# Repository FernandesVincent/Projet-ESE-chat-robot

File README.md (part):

# Projet ESE – Chat Robot  

Le projet de Chat Robot développé dans le cadre de la spécialité ESE dirigée par M.Fiack et supervisée par lui et M. Papazogou s'est achevé le vendredi 16 Janvier 2026. 

Nous allons donc revenir ici sur les différents aspects notables du projet, notamment ceux où notre projet s'est détaché des consignes initiales.

Nous allons donc passer en revue les différentes parties du projet en commençant par une partie sur l'organisation du projet et des tâches attribuées aux différents membres de l'équipe puis nous aborderons la partie Hardware séparée en deux sous parties, l'une pour la modélisation 3D sous Onshape et l'autre pour la conception de PCB sous Kicad. Puis, nous aborderons la partie Software séparée en plusieurs parties, chachune abordant un composant important du projet. 

Par soucis de lisibilité de l'ensemble du document nous n'allons pas détaillé en profondeur toutes les parties et sous parties liées à la mise en place de chaque composant sur le PCB ou à leur programmation. À la place, nous expliquerons brièvement l'ensemble des logiques hardware et software pour ensuite analyser en profondeurs seulement certains aspects de ces parties.

## Organisation du Projet

Le projet a été porté par une équipe de quatres étudiants de 3ème année à l'ENSEA faisant partit de la spécialité ESE, cette équipe est composée de : 

- Vincent FERNANDES
- Paul CAILLAUD
- Kelly LUO
- Yimei Xia

Après diverses discussions au cours du semestre, voici comment ont été attribués les rôles concernant le projet : 

- Vincent : PCB, modélisation/impression 3D, Soudure CMS & THT, TOFs, Moteurs, LED, LiDAR, mise en commun du code sous FreeRTOS
- Paul : Modélisation 3D, cablâge, Soudure CMS & THT, Accéléromètre, Moteurs
- Kelly : Lidar
- Yimei : Accéléromètre

Par ailleurs un README relatant l'avancée à mi-parcours (13 Novembre) est disponible dans le dossier Gestion.

## Hardware

### Modélisation 3D

Pour notre projet, nous avons décidés d'utiliser un pack de batteries Li-ion 2S au lieu du pack de 5 batteries NIMH fournit à la base car cela nous apporte une stabilité de maintient de la tension aux bornes de la batterie ainsi qu'une simplicité de la recharge. En effet, pour recharger les batteries que nous utilisions il nous fallait simplement les connecter à n'importe quelle alimentation stabilisée à 8.4V et non pas un chargeur dédié comme pour les batteries NIMH.

Cela étant, dû au fait d'avoir modifier les batteries nous avons dû adapter notre modélisation 3D. Nous avons donc décider d'inclure la pack de batteries directement dans la base du robot comme présenté ci-dessous afin d'augmenter la stabilité de l'ensemble. Cependant, cela a eu pour effet d'augmenter le diamètre de la base de notre robot passant d'une quinzaine de centrimètre à une vingtaine. De plus, nous avons ajouté un cache sur le dessus de la base pour bloquer la batterie en cas de chute ou autre accident. Finalement nous avons également équipé la base d'un arceau afin d'accueillir un bandeau de LED Neopixel ws2812b. 

<figure style="display:flex; gap:5px;">
  <figure style="text-align:center;">
    
    <figcaption>Base vue du dessus</figcaption>
  </figure>
  <figure style="text-align:center;">
    
    <figcaption>Base vue du dessous</figcaption>
  </figure>
</figure>
<figure style="display:flex; gap:5px;">
  <figure style="text-align:center;">
    
    <figcaption>Support de LED</figcaption>
  </figure>
  <figure style="text-align:center;">
    
    <figcaption>Cache de la batterie</figcaption>
  </figure>
</figure>

Contrairement aux autres robots, nous n'avons fait qu'un unique étage, sur lequel sont placé les 6 TOFs et le LiDAR, afin d'avoir la place entre le cache de la batterie et le sol de cet étage de placer le PCB suspendu par des vis M3 et bloqué par les écrous correspondants.

<figure style="display:flex; gap:16px;">
  <figure style="text-align:center;">
    
    <figcaption>Étage du robot</figcaption>
  </figure>
  <figure style="text-align:center;">
    
    <figcaption>Support de TOF</figcaption>
  </figure>
</figure>

De plus, nous avons également modifier les roues afin d'y inclure non pas un mais deux joints toriques par roue afin, encore une fois, de garantir une meilleur stabilité du robot au vu de sa taille. Cependant, cela complexifie légèrement les virages que peut effectuer le robot là où les lignes droites sont cependant meilleures. 
De plus, pour équilibrer le robot nous utilisons des billes en métal dont le support initial accepte uniquement des vis M2 or nous n'avons pas réussi à trouver des vis de ce diamètre assez longues pour être compatible avec notre modélisation. Ainsi, nous avons recréés des supports inspirés des initiaux mais utilisant des vis M3 car nous les avions à la longueur adéquate et à cela s'ajoute qu'utiliser des vis de plus gros diamètre permet de joindre plus solidement les 2 pièces.

<figure style="display:flex; gap:16px;">
  <figure style="text-align:center">
    
    <figcaption>Roue</figcaption>
  </figure>
  <figure style="text-align:center">
    
    <figcaption>Support de bille</figcaption>
  </figure>
</figure>

### PCB

Pour la conception de PCB nous sommes passés par le logiciel KiCAD et nous en avons créés 4 différents pour certaines raisons que nous expliquerons au fur et à mesure de l'explication générale de chaque PCB.

#### PCB v1

Ce PCB est le premier qui a été designé pour le projet de robot chat. Il inclut notamment les composants de base utiles au bon fonctionnement du robot tel que les drivers de moteurs, l'accéléromètre et les connecteurs pour les TOFs ainsi que celui pour le LiDAR. En effet, pour ce projet nous avons choisis d'utiliser une solution à base de 6 TOFs afin de détecter le vide autour de la table sur laquelle se déplace le robot. Le choix de 6 TOFs a été réfléchis afin d'avoir suffisament de TOFs pour pouvoir repérer le vide peut importe l'orientation du robot au moment d'approcher le bord de table, sans non plus utiliser une quantité non raisonnable de capteurs.

De plus, ce PCB inclut trois nouveaux éléments que l'on a décidé d'ajouter à notre robot. Le premier est un connecteur vers un module MP3 dans le but de jouer un son, défini en amont, à certains moments clés de la présentation. On peut prendre comme exemple le moment où le vide est repéré par un TOF ou bien au moment d'une collision avec un autre robot. 

Le deuxième élément est un bandeau de LED Neopixels commandé par une PWM avec DMA. Le but ici est de venir, tout comme le module MP3, indiquer la réalisation de certaines actions du robot. Par exemple, l'idée principale était d'illuminer une des 96 LEDs du bandeau dès lors que le LiDAR détecte une cible. Certaines LEDs pourraient s'allumer en rouge en direction de cibles non valides alors qu'une LED unique serait allumée en direction de l'objet valide : l'autre robot.

Finalement, le troisième élément est une Raspberry Pi zéro 2W. Nous avons choisis de l'incorporer pour, d'une part, remplacer la connexion bluetooth demandée mais également d'une autre part pour y développer une interface graphique intéractive. Cette dernière permettrait de récupérer les données captées par le robot en temps réel mais également de lui envoyer des instructions, également en temps réel grâce à une lisaion UART.

L'ajout de ces composants nous a obligés à changer le microcontrôleur fourni de base par un STM32G474RET6 possédant, au contraire de l'initial, le nombre suffisant d'HUART accessibles simultanément pour nos besoins.

<figure style="display:flex; gap:16px;">
  <figure style="text-align:center">
    
    <figcaption>Schematic</figcaption>
  </figure>
  <figure style="text-align:center">
    
    <figcaption>PCB Editor</figcaption>
  </figure>
</figure>

Cependant, plusieurs problèmes datant de la conception sous KiCAD sont apparus une fois le PCB soudé et testé. Parmi celles-ci, les plus notables et plus importante sont les suivantes : 

- Oubli de connection de la pin ADDR de l'accéléromètre à GND (ou VCC en fonctiond de l'adresse voulue).
- Inversion des connexions SDA/SCL pour l'I2C de l'accéléromètre.
- Mauvaise connexion du pin Tx du LiDAR à un GPIO simple.
- Mauvaises connexions des pins GPIO des TOFs empêchant leur utilisation en interruption.

Même si, à la fin du projet nous avons pu en partie corriger ces erreurs de différentes façons il nous semblait essentiel de les faire apparaître dans ce compte rendu. Par exemple, nous avons connectés le LiDAR au connecteur de la Pi qui utilise également un UART et nous avons utilisés les TOFs en polling et non en interruption.

#### PCB v1.5

Cette version du PCB a été créée suite à la découverte des erreurs présentes sur la première version. Cette version a été designée dans l'idée d'avoir un PCB purement fonctionnel corrigeant les erreurs du PCB précédent tout en enlevant les éléments non nécessaires ajoutés dans la v1. Nous avons tout de même gardé le même microcontrôleur STM32G474RET6 bien que le nombre de pins soit bien plus important que nécessaire car cela nous a permis de gagné du temps en conception et le PCB a donc pu être réalisé en moins d'une journée.

<figure style="display:flex; gap:16px;">
  <figure style="text-align:center">
    
    <figcaption>Schematic</figcaption>
  </figure>
  <figure style="text-align:center">
    
    <figcaption>PCB Editor</figcaption>
  </figure>
</figure>

Malheureusement, cette version a seulement eu le temps d'arrivée pour le jour exact de la présentation du projet car il y a eu de nombreuses semaines de retard dans la validation finale de la commande contenant ce PCB par le service déidé de l'établissement auprès du fabricant. 

#### PCB v2

Cette version est une version plus avancée du premier PCB, plus petite et comportant plus de composants et fonctionnalités. Parmi tout ces ajouts, les plus sont notables sont l'ajout d'un système de visualisation de la batterie en analogique uniquement, de résistances de shunt associées avec des amplificateurs afin de pouvoir asservir les moteurs en courant. De plus, des connecteurs pour utiliser pleinement le PCB dédié à l'amplificateur audio ainsi qu'un bouton ON-OFF-ON utilisé pour choisir le mode du robot ont été ajoutés au PCB.

<figure style="display:flex; gap:16px;">
  <figure style="text-align:center">
    
    <figcaption>Schematic</figcaption>
  </figure>
</figure>

<figure style="display:flex; gap:16px;">
  <figure style="text-align:center">
    
    <figcaption>Vue 3D Top</figcaption>
  </figure>
  <figure style="text-align:center">
    
    <figcaption>Vue 3D Bottom</figcaption>
  </figure>
</figure>
  
Pour créer le système de surveillance de la batterie, des comparateurs LM339LVRTER ont été utilisés pour comparer la tension réelle de la batterie à une tension de référence qui ne varie pas même si la tension de la batterie diminue. Cette tension de référence a été créée par la mise en série d'un abaisseur de tension (MCP1802T-0902I/OT) permettant une sortie de tension de 0.9V tant que la tension d'entrée est supérieure à 2V et d'un amplificateur de tension (TPS61097A-33DBVR) permettant de ramener la tension à 3.3V qui est donc comparable à la tension réelle passée dans un diviseur de tension. Un module Buck-Boost aurait pu remplacer cette mise en série des deux composants mais nous n'en avons pas trouver permettant d'avoir ces valeurs de tension de manière stable même lorsque la tension réelle approche les 2V. 
Pour afficher le niveau de la batterie un jeu de 12 LEDs CMS a été installé sur le PCB, tant que la tension réelle est supérieure à la tension seuille, la LED associée est allumée mais dès lors que le tension réelle est inférieure à la tension seuille la LED s'éteint. Dans un soucis uniquement visuel les 12 LEDs forment un dégradé allant de vert à rouge.

Malheureusement, cette version a seulement pu être soudée (non testée) avant la présentation du projet car il y a eu de nombreuses semaines de retard dans la validation finale de la commande contenant ce PCB par le service déidé de l'établissement auprès du fabricant. 

#### PCB audio

Ce PCB très simple utilise uniquement un amplificateur audio (LM48100QMHX/NOPB) afin d'amplifier le signal en sortie du module MP3. Ce dernier utilise un câble mini-jack fonctionnant pour une utilisation en connexion directe comme avec un casque audio. Cependant cette sortie mini-jack ne fournit pas assez de puissance pour qu'un haut parleur directement connecté à celle-ci produise un son audible. Il faut donc, entre le haut-parleur et le module MP3, ajouter un amplificateur audio. 

<figure style="display:flex; gap:16px;">
  <figure style="text-align:center">
    
    <figcaption>Schematic</figcaption>
  </figure>
  <figure style="text-align:center">
    
    <figcaption>PCB Editor</figcaption>
  </figure>
</figure>

Cet amplificateur audio a été choisi, tout d'abord pour ses spécificités techniques de 1W/8ohms correspondant excatement à celles de notre haut-parleur. De plus, quand la liste des choix possibles a été suffisament réduite nous avons pris le parti de choisir celui de la marque Texas Instrument car leur documentation est très lisible et compréhensible comparée à celle de leur concurrent. Cela nous permet, par exemple, de réduire le temps passé tant sur la partie hardware que sur la partie software de ce PCB. De plus, La communication I2C de cet l'amplificateur permet de modifier le volume en sortie sur 28 niveaux différents, ce qui est encore un autre avantage de ce dernier. Le seul "inconvénient", s'il faut en citer un, est le fait que le composant soit de base dans un état de veille et qu'il doit être "réveillé" grâce à l'écriture dans l'un de ses registres via la communication I2C, ce qui oblige à toujours devoir le connecté en I2C pour qu'il fonctionne.

## Software 

Des précisions supplémentaires pour les parties de Kelly LUO sont disponibles [ici](/software/README.md).

### LiDAR

Le LiDAR est l'élément qui permet au robot de :
- détecter la cible à pourchasser lorsque le robot est en mode chat.
- détecter la cible à fuir lorsque le robot est en mode souris.

Le YDLIDAR X2, fournit et imposé, communique en liaison UART avec le MCU du PCB. Comme il n'a qu'une seule broche Tx pour cette liaison, nous avons décidé de réglé l'UART en mode Half-Duplex car comme nous ne faisons que recevoir des données il n'est pas nécessaire d'avoir une liaison utilisant Tx et Rx.

Ce LiDAR transmet 3000 trames, chacune contenant plusieurs points, par seconde et effectue entre 5 et 8 tours par secondes en fonction de la tension (ou PWM) appliquée sur le pin M_CTR du LiDAR. Pour avoir une meilleure précision nous avons préférés travailler avec une vitesse entre 6 et 8 tours par secondes.

Le code associé au LiDAR est disponible en 2 versions, l'un créée par Kelly LUO est fonctionnelle sur la nucleo-L476RG mais pas sur le MCU du projet et est disponible dans le dossier : "lidar_nucleo". La seconde version créée par Vincent FERNANDES est adaptée au MCU du projet mais n'a pas pu être finie à temps pour la présentation du projet.

Ci-dessous, les explications du code de la première version par Kelly LUO : 
  
La YDLIDAR X2 est interfacé en UART avec notre micro controleur et les données envoyés suit un protocole particulier.
Pour atteindre notre objectif, il nous a d'abord fallut traiter les informations reçu. Les trames reçu comportais beaucoup de valeur nulle, qui ne correspondait pas à un distance nulle, mais plus à un signal envoyé et non reçu. Nous avons décider de stocker les distances de plusieurs trames, pour avoir une image de l'environnement plus complète. Ensuite, nous avons mis en place un algorithme de détection de cible. L'algorithme mis en place est assez précis, mais je pense qu'il est lourd en calcul. Peut être qu'un algorithme plus simple aurait été plus adapté pour notre utilisation.

Ci-dessous, les explications du code de la seconde version par Vincent FERNANDES : 

L'objectif est ici de repérer une cible déterminée comme valide et d'agir en conséquence en fonction du mode (chat ou souris) dans lequel se trouve le robot. 

Pour effectuer ce travail, nous avons choisis d'analyser tour par tour ce que percevait le LiDAR. Pour ce faire nous surveillons un bit précis du protocole du LiDAR qui est à 1 lorsque qu'un nouveau tour est entammé.

Pour chaque tour nous traitons les trames et en récupérons l'ensemble des points ayant chacun les attributs "distance" et "angle", ce qui nous permet de "dessiner" un cercle de ce que perçoit le LiDAR à chacun de ces tours. 

Afin d'éviter d'inclure des distances éronnées dans ce cercle nous limitons la distance maximale tel que si la distance d'un point est perçue supérieure à celle-ci alors nous lui attribuons pour valeur celle de la distance maximale choisie. 

Pour déterminer le nombre d'objets et leur position respectives nous utilisons l'algorithme suivant : 

1. Dans une boucle allant du premier au dernier point du cercle, choisir un point i.
2. Comparer la valeur de distance de ce point i à un seuil.
3. Si la distance du point i est inférieure au seuil alors faire de même pour les 4 points suivants, moyenner et comparer la moyenne au seuil sinon passer au point suivant.
4. Si la valeur moyennée est également inférieure au seuil alors enregistrer le point i comme premier point de l'objet j puis enregistrer tout les points qui suivent comme faisant partis de l'objet jusqu'à ce qu'un point i+n contredisant l'étape 3 apparaisse, ce point est alors enregistrer comme le point de fin de l'objet.
5. Répeter cette boucle pour tout les points du cercle.
6. Pour chaque objet enregistré, déterminer le diamètre réel de celui-ci grâce aux équations d'Al-Kashi.
7. Si le diamètre calculé est égal à un diamètre prédéfinis avec une certaine incertitude alors l'objet est considéré comme valide sinon il est considéré comme ne l'étant pas.
8. Pour l'objet valide, récupérer le point de l'objet ayant la distance la plus courte au LiDAR.
9. Diriger le robot en direction de l'angle associé au point récupérer à l'étape précédente.
10. Si plusieurs objets sont valides, calculer la distance moyenne de leurs points et se diriger vers le point de l'étape 8 pour l'objet ayant la moyenne de distance la plus basse.
11. À la fin du traitement du tour, vider l'ensemble des buffers puis recommencer.

Cet algorithme est assez lourd mais cela ne pose pas de problème majeur dans notre cas particulier car le STM32G474RET6 possède suffisament de RAM pour le traiter. Avec plus de temps, un algorithme plus léger aurait surement pu être trouvé.

### Moteurs

Les moteurs sont un élement essentiel du projet puisqu'il faut que le robot puisse se déplacer sur la table. Nous avons à notre disposition des moteurs FIT0520 qui seront chacuns pilotés par un driver. Nous avons fait le choix de faire une structure par moteur, cette dernière contenant le timer qui correspond à la PWM qui sera appliquée, la direction (Forward ou Reverse), la vitesse ainsi que le channel pour le timer. Un deuxième type de structure a ensuite été créé, celle du PID qui contient les valeurs des coefficients du correcteur afin de bien asservir le moteur. Il faut cependant noter que nous n'avons pas eu le temps de bien mettre en place le correcteur, les valeures ne sont donc pas les bonnes. Nous avons ensuite eu l'idée d'une autre structure appelée Robot qui comprend les deux moteurs et les PID, nous ne nous en sommes au final pas servis car nous controlions chaque moteur séparément.

<figure style="display:flex; gap:16px;">
  <figure style="text-align:center">
    
    <figcaption>Structure du Robot</figcaption>
  </figure>
  <figure style="text-align:center">
    
    <figcaption>Structure d'un moteur</figcaption>
  </figure>
  <figure style="text-align:center">
    
    <figcaption>Structure du PID</figcaption>
  </figure>
</figure>

Dans le .c, on commence par initialiser chaque moteur, en fournissant le timer ainsi qu'un channel pour "Forward" et un autre pour "Reverse", une vitesse nulle et la direction Forward. (On retrouve aussi les initialisations des autres structures).
Il a ensuite fallu réaliser les différentes fonctions des moteurs, start, stop, ainsi que les changements de direction et les changements de vitesse. En exemple, pour la fonction moteur_forward, le code commence par vérifier quel moteur appelle la fonction, ensuite la PWM correspondante au bon moteur Forward est démarrée. La direction Reverse est éteinte, et ce même si le moteur était arrété précédement.

<figure style="display:flex; gap:16px;">
  <figure style="text-align:center">
    
    <figcaption>Fonction d'initialisation</figcaption>
  </figure>
  <figure style="text-align:center">
    
    <figcaption>Fonction de choix de la vitesse</figcaption>
  </figure>
  <figure style="text-align:center">
    
    <figcaption>Fonction rampe de vitesse</figcaption>
  </figure>
</figure>

<figure style="display:flex; gap:16px;">
  <figure style="text-align:center">
    
    <figcaption>Fonction pour avancer</figcaption>
  </figure>
  <figure style="text-align:center">
    
    <figcaption>Fonction de recul</figcaption>
  </figure>
  <figure style="text-align:center">
    
    <figcaption>Fonction pour tourner</figcaption>
  </figure>
</figure>

### TOF

Pour ce projet, nous utilisons 6 TOFs VL53L0X. Comme notre MCU possède un nombre de pins suffisants nous n'avons pas eu besoin de passer par un multiplexeur I2C pour travailler indépendamment avec chacun des six TOFs. En effet, dans la plupart des cas un multiplexeur est utilisé car ces TOFs ont une adresse fixe identique qui peut être modifiée mais nécessite une ligne supplémentaire par TOF pour connecter le pin XSHUT permettant de mettre en veille ou de reveillé un TOF. En effet, avant toute chose, pour travailler avec les 6 TOFs nous avons besoin de les initialisés avec chacun une adresses différente, pour ce faire nous utilisons les fonctions suivantes : 

<figure style="display:flex; gap:16px;">
  <figure style="text-align:center">
    
    <figcaption>Structure des nouvelles adresses des TOFs</figcaption>
  </figure>
  <figure style="text-align:center">
    
    <figcaption>Fonction de changement d'adresse</figcaption>
  </figure>
  <figure style="text-align:center">
    
    <figcaption>Fonction d'initialisation d'un TOF</figcaption>
  </figure>
</figure>
<figure style="display:flex; gap:16px;">
  <figure style="text-align:center">
    
    <figcaption>Fonction d'initialisation de tous les TOFs</figcaption>
  </figure>
</figure>

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
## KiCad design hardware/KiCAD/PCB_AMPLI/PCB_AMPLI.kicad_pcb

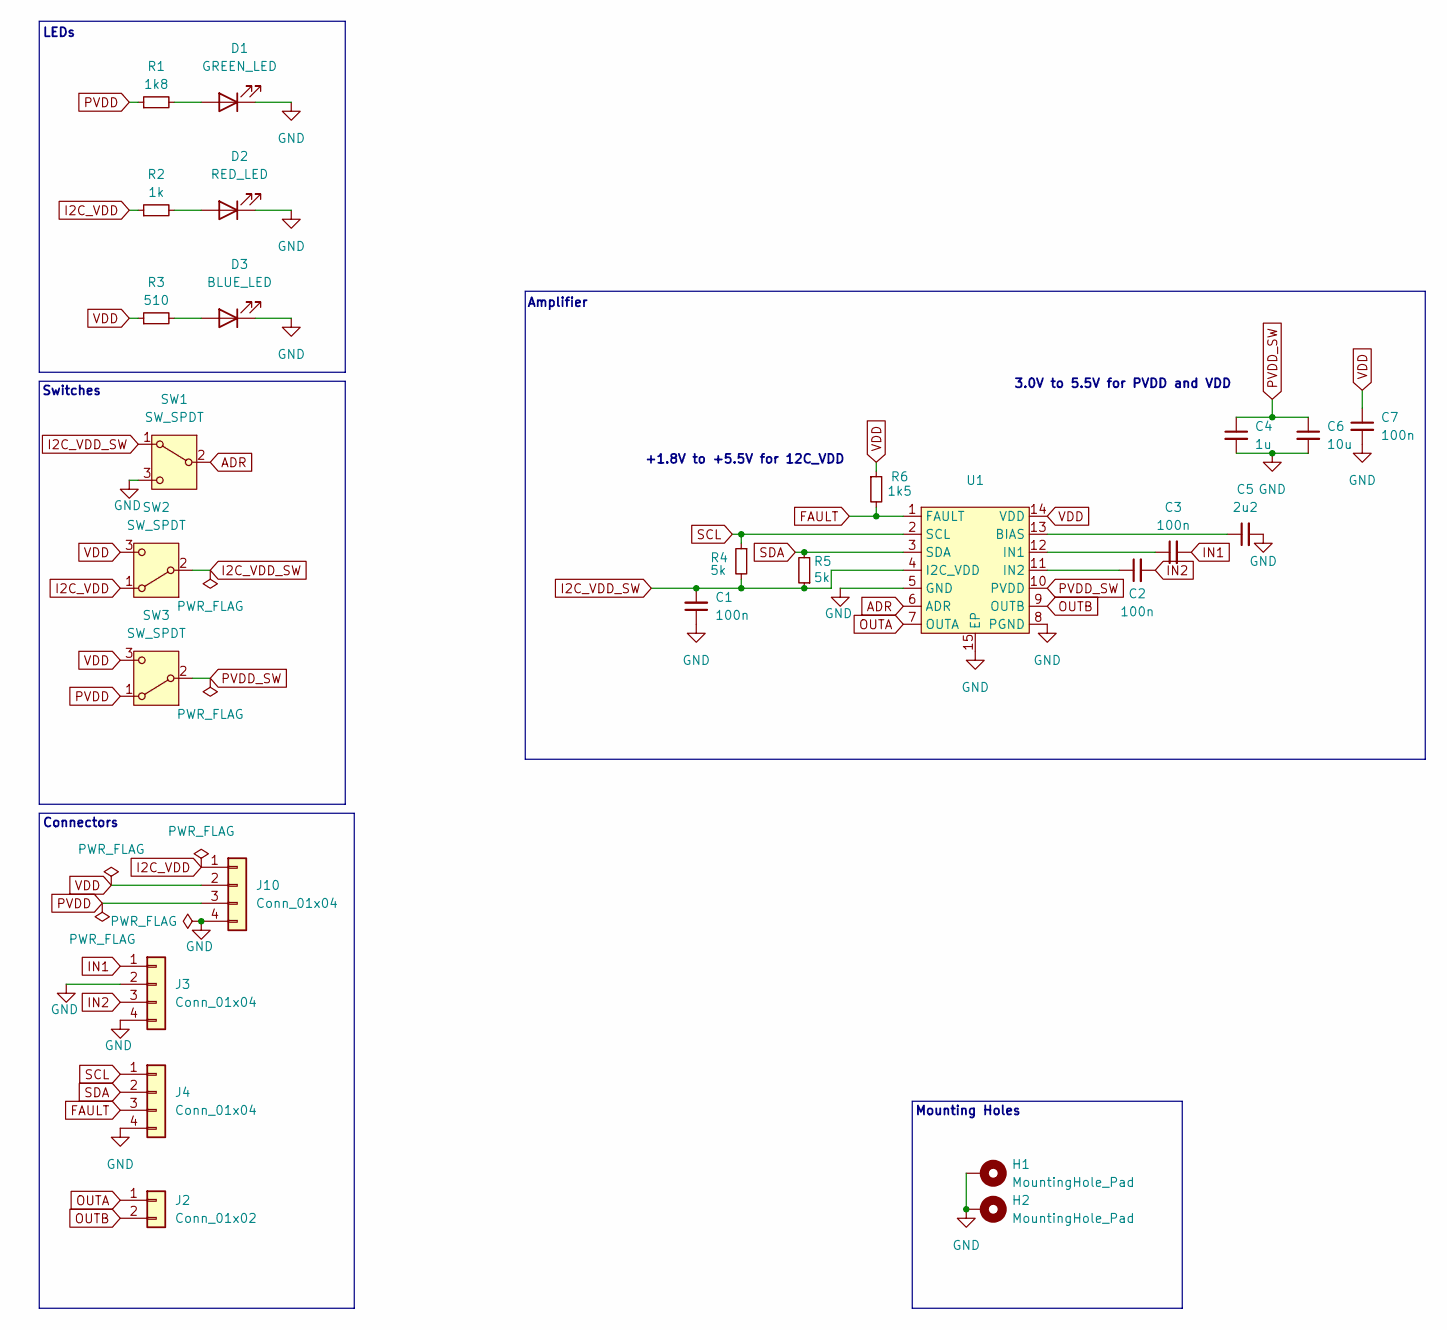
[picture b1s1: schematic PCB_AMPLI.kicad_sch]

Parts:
C1, C2, C3, C7: 100n; C_0402_1005Metric
C4: 1u; C_0603_1608Metric
C5: 2u2; C_0603_1608Metric
C6: 10u; C_0603_1608Metric
D1: GREEN_LED; LED_0603_1608Metric; MPN 150060GS55040
D2: RED_LED; LED_0603_1608Metric; MPN 150060RS55040
D3: BLUE_LED; LED_0603_1608Metric; MPN 150060BS55040
H1, H2: MountingHole_Pad; MountingHole_3.2mm_M3_Pad
J2: Conn_01x02; PinHeader_1x02_P2.54mm_Vertical
J3, J4, J10: Conn_01x04; PinHeader_1x04_P2.54mm_Vertical
R1: 1k8; R_0402_1005Metric
R2: 1k; R_0402_1005Metric
R3: 510; R_0402_1005Metric
R4, R5: 5k; R_0402_1005Metric
R6: 1k5; R_0402_1005Metric
SW1: SW_SPDT; 450406020024; MPN 450406020024
SW2, SW3: SW_SPDT; 450406020024
U1: HTSSOP-14-1EP_4.4x5mm_P0.65mm_EP3.4x5mm_Mask3x3.1mm; MPN LM48100QMHX/NOPB

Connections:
ADR: SW1.2 (B), U1.6 (ADR)
FAULT: J4.3, R6.2, U1.1 (FAULT)
GND: C1.1, C4.2, C5.2, C6.2, C7.2, D1.1 (K), D2.1 (K), D3.1 (K), H1.1, H2.1, J3.2, J3.4, J4.4, J10.4, SW1.3 (C), U1.5 (GND), U1.8 (PGND), U1.15 (EP)
I2C_VDD: J10.1, R2.1, SW2.1 (A)
I2C_VDD_SW: C1.2, R4.2, R5.1, SW1.1 (A), SW2.2 (B), U1.4 (I2C_VDD)
IN1: C3.2, J3.1
IN2: C2.2, J3.3
unnamed: D1.2 (A), R1.2
unnamed: D2.2 (A), R2.2
unnamed: D3.2 (A), R3.2
unnamed: C5.1, U1.13 (BIAS)
unnamed: C3.1, U1.12 (IN1)
unnamed: C2.1, U1.11 (IN2)
OUTA: J2.1, U1.7 (OUTA)
OUTB: J2.2, U1.9 (OUTB)
PVDD: J10.3, R1.1, SW3.1 (A)
PVDD_SW: C4.1, C6.1, SW3.2 (B), U1.10 (PVDD)
SCL: J4.1, R4.1, U1.2 (SCL)
SDA: J4.2, R5.2, U1.3 (SDA)
VDD: C7.1, J10.2, R3.1, R6.1, SW2.3 (C), SW3.3 (C), U1.14 (VDD)

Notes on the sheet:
+1.8V to +5.5V for 12C_VDD
Mounting Holes
Switches
3.0V to 5.5V for PVDD and VDD
LEDs
Connectors
Amplifier

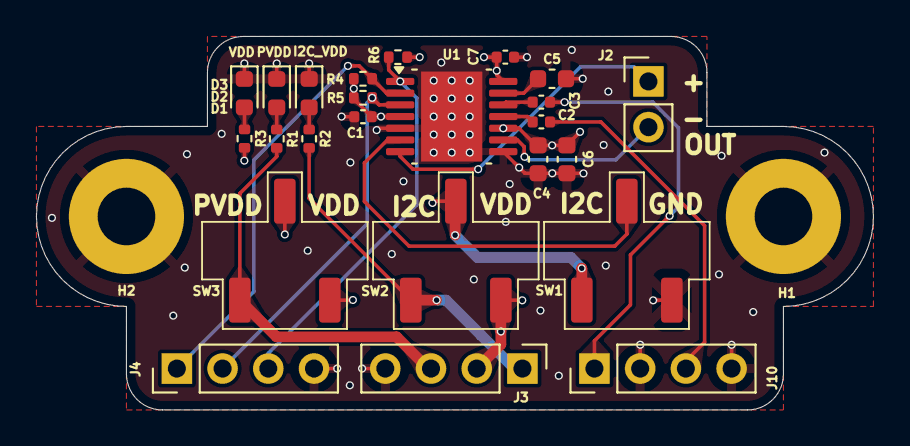
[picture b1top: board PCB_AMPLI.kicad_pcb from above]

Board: 4 copper layers, 46.5 x 20.8 mm, 26 parts (0 on the bottom side), 20 nets.

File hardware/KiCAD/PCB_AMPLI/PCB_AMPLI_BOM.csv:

"Reference","Qty","Value"
"C1,C2,C3,C7","4","100n"
"C4","1","1u"
"C5","1","2u2"
"C6","1","10u"
"D1","1","GREEN_LED"
"D2","1","RED_LED"
"D3","1","BLUE_LED"
"H1,H2","2","MountingHole_Pad"
"J2","1","Conn_01x02"
"J3,J4,J10","3","Conn_01x04"
"R1","1","1k8"
"R2","1","1k"
"R3","1","510"
"R4,R5","2","5k"
"R6","1","1k5"
"SW1,SW2,SW3","3","SW_SPDT"
"U1","1","~"

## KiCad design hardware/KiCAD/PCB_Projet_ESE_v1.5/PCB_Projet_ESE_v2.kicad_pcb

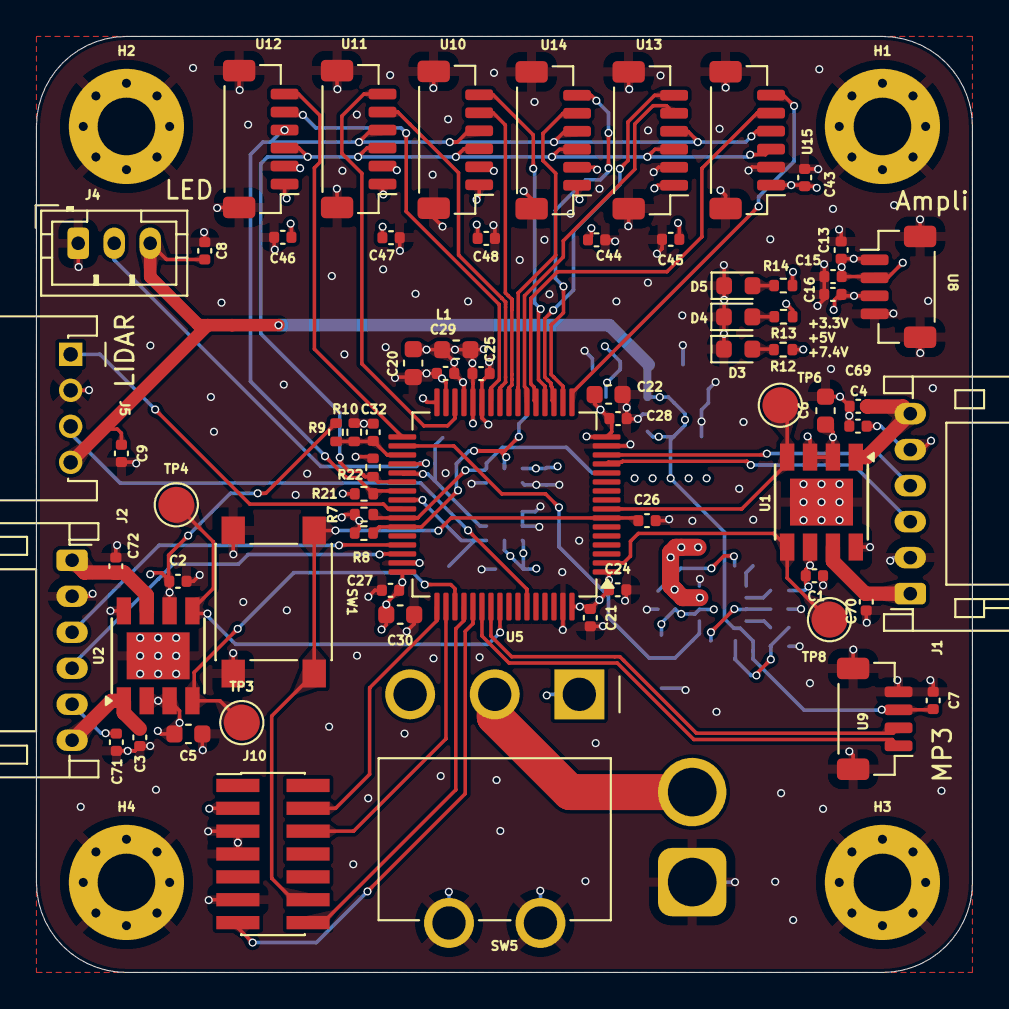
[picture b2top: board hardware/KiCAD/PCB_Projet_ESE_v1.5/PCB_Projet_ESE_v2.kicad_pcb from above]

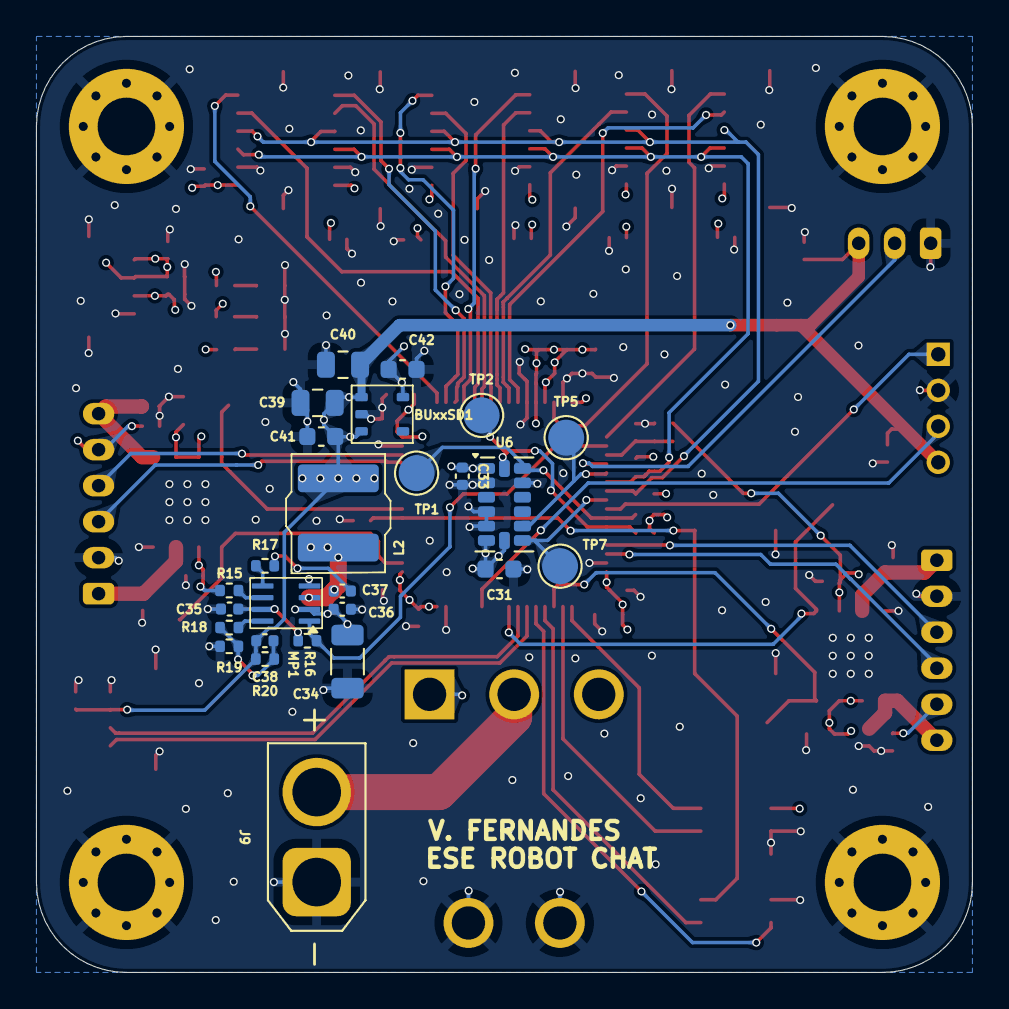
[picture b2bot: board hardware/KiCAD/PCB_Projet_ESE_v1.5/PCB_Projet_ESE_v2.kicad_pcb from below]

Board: 4 copper layers, 52.0 x 52.0 mm, 98 parts (26 on the bottom side), 57 nets.

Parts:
BUxxSD1: SSOP5_BUxxSD5
C1, C2, C3, C4, C7, C8, C9, C13, C15, C16, C21, C24, C25, C26, C27, C28, C32, C33, C35, C36, C37, C43, C44, C45, C46, C47, C48, C69, C70, C71, C72: 100n; C_0402_1005Metric
C5, C6, C20: 4u7; C_0603_1608Metric
C22, C30, C31, C41, C42: 1u; C_0603_1608Metric
C29: 10n; C_0402_1005Metric
C34: 22u; C_1206_3216Metric
C38: 15p; C_0402_1005Metric
C39, C40: 22u; C_0805_2012Metric
D3, D4, D5: LED; LED_0603_1608Metric
H1, H2, H3, H4: MountingHole_Pad; MountingHole_3.2mm_M3_Pad_Via
J1, J2: Conn_01x06; JST_PH_S6B-PH-K_1x06_P2.00mm_Horizontal
J4: Conn_01x03; JST_PH_B3B-PH-K_1x03_P2.00mm_Vertical
J5: Conn_01x04; J_Wurth_WR-WTB_62000411722
J9: Conn_01x02; AMASS_XT30U-M_1x02_P5.0mm_Vertical
J10: Conn_ST_STDC14; PinHeader_2x07_P1.27mm_Vertical_SMD
L1: 39n; L_0603_1608Metric
L2: 4u7; 74404054068
MP1: TSOT23-8
R7, R8, R21, R22: 4k7; R_0402_1005Metric
R9: 56k; R_0402_1005Metric
R10, R18: 16k; R_0402_1005Metric
R12: 2k7; R_0402_1005Metric
R13: 1k6; R_0402_1005Metric
R14: 820; R_0402_1005Metric
R15, R16: 100k; R_0402_1005Metric
R17: 20; R_0402_1005Metric
R19: 7k68; R_0402_1005Metric
R20: 40k2; R_0402_1005Metric
SW1: SW_SPST
SW5: SW_SPDT; SW_Wurth_WS-TOTV_472123020421
TP1, TP2, TP3, TP4, TP5, TP6, TP7, TP8: TestPoint; TestPoint_Pad_D2.0mm
U1, U2: ZXBM5210-SP; Diodes_SO-8EP
U5: STM32G474RETx; LQFP-64_10x10mm_P0.5mm
U6: ADXL343; LGA-14_3x5mm_P0.8mm_LayoutBorder1x6y
U8, U9: JST_SH_4_Vertical
U10, U11, U12, U13, U14, U15: JST_SH_6_Vertical

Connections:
+3.3V: BUxxSD1.5 (Vout), C3.1, C4.1, C13.2, C15.2, C20.1, C21.1, C22.1, C24.1, C25.1, C27.1, C28.1, C29.1, C30.2, C31.2, C33.1, C42.1, C43.1, C44.1, C45.1, C46.1, C47.1, C48.1, J1.5, J2.5, J10.3 (VCC), L1.1, L1.2, R7.1, R8.1, R14.1, R21.1, R22.1, U5.1 (VBAT), U5.16 (VDD), U5.28 (VREF+), U5.29 (VDDA), U5.32 (VDD), U5.48 (VDD), U5.64 (VDD), U6.1 (Vdd_I/O), U6.6 (Vs), U6.7 (~CS), U8.1, U8.2, U10.1, U11.1, U12.1, U13.1, U14.1, U15.1
+5V: BUxxSD1.1 (Vin), BUxxSD1.3 (STBY), C7.2, C8.1, C9.1, C16.2, C38.2, C39.2, C40.2, C41.1, J4.3, J5.4, L2.2, R13.1, R20.2, U8.3, U9.3
+7.4V: C1.1, C2.1, C5.2, C6.2, C34.2, C36.2, MP1.2 (IN), R9.1, R12.1, R15.1, SW5.1, U1.2 (VM), U1.3 (VDD), U1.6 (VREF), U2.2 (VM), U2.3 (VDD), U2.6 (VREF)
ACCEL_INT1: TP7.1, U5.40 (PC8), U6.8 (INT1)
ACCEL_INT2: TP5.1, U5.37 (PB15), U6.9 (INT2)
ACCEL_SCL: R8.2, TP2.1, U5.43 (PA9), U6.14 (SCL/SCLK)
ACCEL_SDA: R7.2, TP1.1, U5.42 (PA8), U6.13 (SDA/SDI/SDIO)
ADC_Bat: C32.1, R9.2, R10.1, U5.35 (PB13)
Encodeur_1_Phase_A: J1.3, U5.13 (PA1)
Encodeur_1_Phase_B: J1.4, U5.14 (PA2)
Encodeur_2_Phase_A: J2.3, U5.45 (PA11)
Encodeur_2_Phase_B: J2.4, U5.46 (PA12)
GND: BUxxSD1.2 (GND), C1.2, C2.2, C3.2, C4.2, C5.1, C6.1, C7.1, C8.2, C9.2, C13.1, C15.1, C16.1, C20.2, C21.2, C22.2, C24.2, C25.2, C26.2, C27.2, C28.2, C29.2, C30.1, C31.1, C32.2, C33.2, C34.1, C35.2, C36.1, C39.1, C40.1, C41.2, C42.2, C43.2, C44.2, C45.2, C46.2, C47.2, C48.2, C69.1, C70.2, C71.1, C72.2, D3.1 (K), D4.1 (K), D5.1 (K), H1.1, H2.1, H3.1, H4.1, J1.2, J2.2, J4.1, J5.2, J9.1, J10.5 (GND), J10.7 (GND), J10.11 (GNDDetect), MP1.4 (GND), R10.2, R19.2, SW1.2 (B), SW5.G1, SW5.G2, U1.8 (GND), U1.9 (GND), U2.8 (GND), U2.9 (GND), U5.15 (VSS), U5.27 (VSSA), U5.31 (VSS), U5.47 (VSS), U5.63 (VSS), U6.2 (GND), U6.4 (GND), U6.5 (GND), U6.12 (SDO/ADDR), U8.4, U8.5 (GND), U8.6 (GND), U9.4, U9.5 (GND), U9.6 (GND), U10.2, U10.7 (GND), U10.8 (GND), U11.2, U11.7 (GND), U11.8 (GND), U12.2, U12.7 (GND), U12.8 (GND), U13.2, U13.7 (GND), U13.8 (GND), U14.2, U14.7 (GND), U14.8 (GND), U15.2, U15.7 (GND), U15.8 (GND)
Moteur_1_FWD: TP6.1, U1.4 (FWD), U5.8 (PC0)
Moteur_1_OUT+: C69.2, J1.6, U1.1 (OUT1)
Moteur_1_OUT-: C70.1, J1.1, U1.7 (OUT2)
Moteur_1_REV: TP8.1, U1.5 (REV), U5.2 (PC13)
Moteur_2_FWD: TP3.1, U2.4 (FWD), U5.51 (PA15)
Moteur_2_OUT+: C71.2, J2.6, U2.1 (OUT1)
Moteur_2_OUT-: C72.1, J2.1, U2.7 (OUT2)
Moteur_2_REV: TP4.1, U2.5 (REV), U5.56 (PB3)
NRST: C26.1, J10.12 (~RST), SW1.1 (A), U5.7 (PG10)
unnamed: C37.1, R17.2
unnamed: C38.1, R18.1, R19.1, R20.1
unnamed: D3.2 (A), R12.2
unnamed: D4.2 (A), R13.2
unnamed: D5.2 (A), R14.2
unnamed: J9.2, SW5.2
unnamed: MP1.5 (BST), R17.1
unnamed: MP1.6 (EN/SYNC), R15.2
unnamed: MP1.8 (FB), R18.2
unnamed: C37.2, L2.1, MP1.3 (SW)
unnamed: C35.1, MP1.7 (VCC), R16.1
PG: MP1.1 (PG), R16.2, U5.34 (PB12)
PWM_LED: J4.2, U5.36 (PB14)
PWM_LIDAR_MCTR: J5.1, U5.41 (PC9)
SWCLK: J10.6 (JCLK/SWCLK), U5.50 (PA14)
SWDIO: J10.4 (JTMS/SWDIO), U5.49 (PA13)
TOF_1_GPIO: U5.26 (PB2), U12.5
TOF_1_XSHUT: U5.33 (PB11), U12.6
TOF_2_GPIO: U5.25 (PB1), U11.5
TOF_2_XSHUT: U5.30 (PB10), U11.6
TOF_3_GPIO: U5.24 (PB0), U10.5
TOF_3_XSHUT: U5.20 (PA6), U10.6
TOF_4_GPIO: U5.22 (PC4), U13.5
TOF_4_XSHUT: U5.19 (PA5), U13.6
TOF_5_GPIO: U5.23 (PC5), U14.5
TOF_5_XSHUT: U5.18 (PA4), U14.6
TOF_6_GPIO: U5.21 (PA7), U15.5
TOF_6_XSHUT: U5.17 (PA3), U15.6
TOF_SCL: R22.2, U5.38 (PC6), U10.3, U11.3, U12.3, U13.3, U14.3, U15.3
TOF_SDA: R21.2, U5.39 (PC7), U10.4, U11.4, U12.4, U13.4, U14.4, U15.4
UART_Debug_RX: J10.13 (VCP_RX), U5.53 (PC11)
UART_Debug_TX: J10.14 (VCP_TX), U5.52 (PC10)
UART_LIDAR_TX_HD: J5.3, U5.59 (PB6)
UART_mp3_RX: U5.55 (PD2), U9.2
UART_mp3_TX: U5.54 (PC12), U9.1

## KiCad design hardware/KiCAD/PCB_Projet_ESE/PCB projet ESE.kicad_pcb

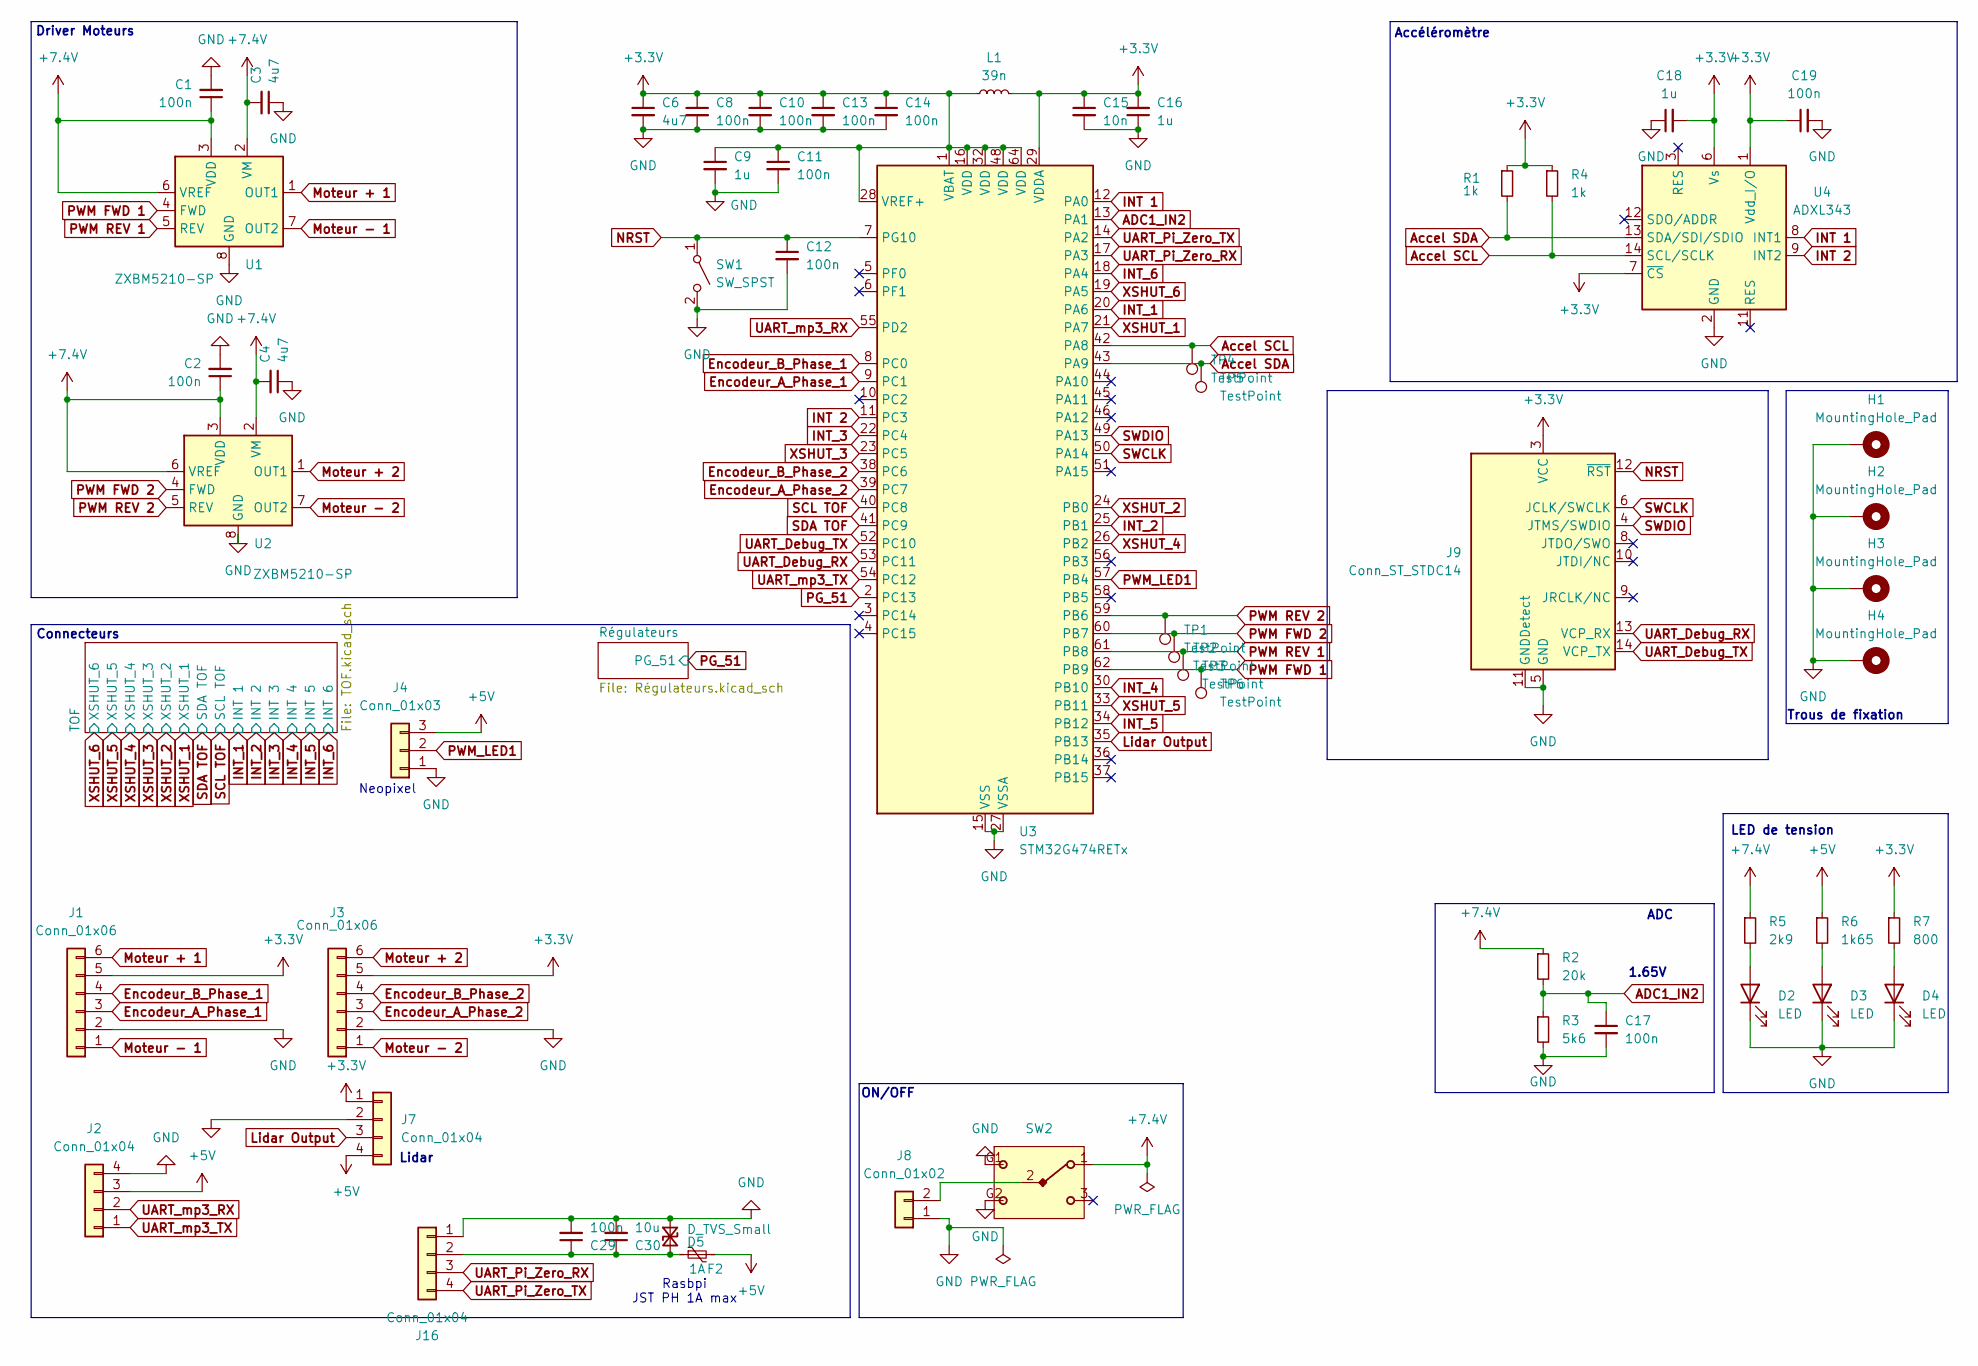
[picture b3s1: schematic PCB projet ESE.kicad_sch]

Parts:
C1, C2, C8, C10, C11, C12, C13, C14, C17, C19, C29: 100n; C_0402_1005Metric
C3, C4, C6: 4u7; C_0603_1608Metric
C9, C16, C18: 1u; C_0603_1608Metric
C15: 10n; C_0402_1005Metric
C30: 10u; C_0603_1608Metric
D2, D3, D4: LED; LED_0603_1608Metric
D5: D_TVS_Small; D_SOD-523; MPN VESD05A1-02V-G3-08
F2: 1A; Fuse_2920_7451Metric; MPN 0ZAF0013FF28
H1, H2, H3, H4: MountingHole_Pad; MountingHole_3.2mm_M3_Pad_Via
J1, J3: Conn_01x06; JST_PH_S6B-PH-K_1x06_P2.00mm_Horizontal
J2: Conn_01x04; JST_SH_BM04B-SRSS-TB_1x04-1MP_P1.00mm_Vertical
J4: Conn_01x03; JST_PH_B3B-PH-K_1x03_P2.00mm_Vertical
J7, J16: Conn_01x04; JST_PH_B4B-PH-K_1x04_P2.00mm_Vertical
J8: Conn_01x02; AMASS_XT30U-M_1x02_P5.0mm_Vertical
J9: Conn_ST_STDC14; PinHeader_2x07_P1.27mm_Vertical_SMD; MPN STLINK-V3MINIE
L1: 39n; L_0603_1608Metric
R1, R4: 1k; R_0402_1005Metric
R2: 20k; R_0402_1005Metric
R3: 5k6; R_0402_1005Metric
R5: 2k9; R_0402_1005Metric
R6: 1k65; R_0402_1005Metric
R7: 800; R_0402_1005Metric
SW1: SW_SPST; MPN 430182070816
SW2: 472121010111; SW_Wurth_WS-TOTV_472123020421; Part Number 472121010111
TP1, TP2, TP3, TP4, TP5, TP6: TestPoint; TestPoint_Pad_D1.0mm
U1, U2: ZXBM5210-SP; Diodes_SO-8EP; MPN ZXBM5210-SP-13
U3: STM32G474RETx; LQFP-64_10x10mm_P0.5mm
U4: ADXL343; LGA-14_3x5mm_P0.8mm_LayoutBorder1x6y; MPN ADXL343BCCZ-RL

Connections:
+3.3V: C6.1, C8.1, C9.1, C10.1, C11.1, C13.1, C14.1, C15.1, C16.2, C18.2, C19.1, J1.5, J3.5, J7.1, J9.3 (VCC), L1.1, L1.2, R1.1, R4.1, R7.1, U3.1 (VBAT), U3.16 (VDD), U3.28 (VREF+), U3.29 (VDDA), U3.32 (VDD), U3.48 (VDD), U3.64 (VDD), U4.1 (Vdd_I/O), U4.6 (Vs), U4.7 (~CS); also elsewhere on the board
+5V: F2.2, J2.3, J4.3, J7.4, R6.1; also elsewhere on the board
+7.4V: C1.1, C2.1, C3.2, C4.2, R2.1, R5.1, SW2.1, U1.2 (VM), U1.3 (VDD), U1.6 (VREF), U2.2 (VM), U2.3 (VDD), U2.6 (VREF); also elsewhere on the board
/5V_Rpi: C29.1, C30.1, D5.2 (A2), F2.1, J16.2
ADC1_IN2: C17.1, R2.2, R3.1, U3.13 (PA1)
Accel SCL: R4.2, TP4.1, U3.42 (PA8), U4.14 (SCL/SCLK); also elsewhere on the board
Accel SDA: R1.2, TP5.1, U3.43 (PA9), U4.13 (SDA/SDI/SDIO); also elsewhere on the board
Encodeur_A_Phase_1: J1.3, U3.9 (PC1)
Encodeur_A_Phase_2: J3.3, U3.39 (PC7)
Encodeur_B_Phase_1: J1.4, U3.8 (PC0)
Encodeur_B_Phase_2: J3.4, U3.38 (PC6)
GND: C1.2, C2.2, C3.1, C4.1, C6.2, C8.2, C9.2, C10.2, C11.2, C12.2, C13.2, C14.2, C15.2, C16.1, C17.2, C18.1, C19.2, C29.2, C30.2, D2.1 (K), D3.1 (K), D4.1 (K), D5.1 (A1), H1.1, H2.1, H3.1, H4.1, J1.2, J2.4, J2.MP, J3.2, J4.1, J7.2, J8.1, J9.5 (GND), J9.7 (GND), J9.11 (GNDDetect), J16.1, R3.2, SW1.2 (B), SW2.G1, SW2.G2, U1.8 (GND), U1.9 (GND), U2.8 (GND), U2.9 (GND), U3.15 (VSS), U3.27 (VSSA), U3.31 (VSS), U3.47 (VSS), U3.63 (VSS), U4.2 (GND), U4.4 (GND), U4.5 (GND); also elsewhere on the board
INT 1: U3.12 (PA0), U4.8 (INT1)
INT 2: U3.11 (PC3), U4.9 (INT2)
INT_1: U3.20 (PA6); also elsewhere on the board
INT_2: U3.25 (PB1); also elsewhere on the board
INT_3: U3.22 (PC4); also elsewhere on the board
INT_4: U3.30 (PB10); also elsewhere on the board
INT_5: U3.34 (PB12); also elsewhere on the board
INT_6: U3.18 (PA4); also elsewhere on the board
Lidar Output: J7.3, U3.35 (PB13)
Moteur + 1: J1.6, U1.1 (OUT1)
Moteur + 2: J3.6, U2.1 (OUT1)
Moteur - 1: J1.1, U1.7 (OUT2)
Moteur - 2: J3.1, U2.7 (OUT2)
NRST: C12.1, J9.12 (~RST), SW1.1 (A), U3.7 (PG10)
unnamed: D2.2 (A), R5.2
unnamed: D3.2 (A), R6.2
unnamed: D4.2 (A), R7.2
unnamed: J8.2, SW2.2
PG_51: U3.2 (PC13); also elsewhere on the board
PWM FWD 1: TP6.1, U1.4 (FWD), U3.62 (PB9); also elsewhere on the board
PWM FWD 2: TP2.1, U2.4 (FWD), U3.60 (PB7); also elsewhere on the board
PWM REV 1: TP3.1, U1.5 (REV), U3.61 (PB8); also elsewhere on the board
PWM REV 2: TP1.1, U2.5 (REV), U3.59 (PB6); also elsewhere on the board
PWM_LED1: J4.2, U3.57 (PB4)
SCL TOF: U3.40 (PC8); also elsewhere on the board
SDA TOF: U3.41 (PC9); also elsewhere on the board
SWCLK: J9.6 (JCLK/SWCLK), U3.50 (PA14)
SWDIO: J9.4 (JTMS/SWDIO), U3.49 (PA13)
UART_Debug_RX: J9.13 (VCP_RX), U3.53 (PC11)
UART_Debug_TX: J9.14 (VCP_TX), U3.52 (PC10)
UART_Pi_Zero_RX: J16.3, U3.17 (PA3)
UART_Pi_Zero_TX: J16.4, U3.14 (PA2)
UART_mp3_RX: J2.2, U3.55 (PD2)
UART_mp3_TX: J2.1, U3.54 (PC12)
XSHUT_1: U3.21 (PA7); also elsewhere on the board
XSHUT_2: U3.24 (PB0); also elsewhere on the board
XSHUT_3: U3.23 (PC5); also elsewhere on the board
XSHUT_4: U3.26 (PB2); also elsewhere on the board
XSHUT_5: U3.33 (PB11); also elsewhere on the board
XSHUT_6: U3.19 (PA5); also elsewhere on the board

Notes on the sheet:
Driver Moteurs
Connecteurs
Lidar
ADC
Rasbpi JST PH 1A max
Trous de fixation
Accéléromètre
ON/OFF
Neopixel
LED de tension
1.65V

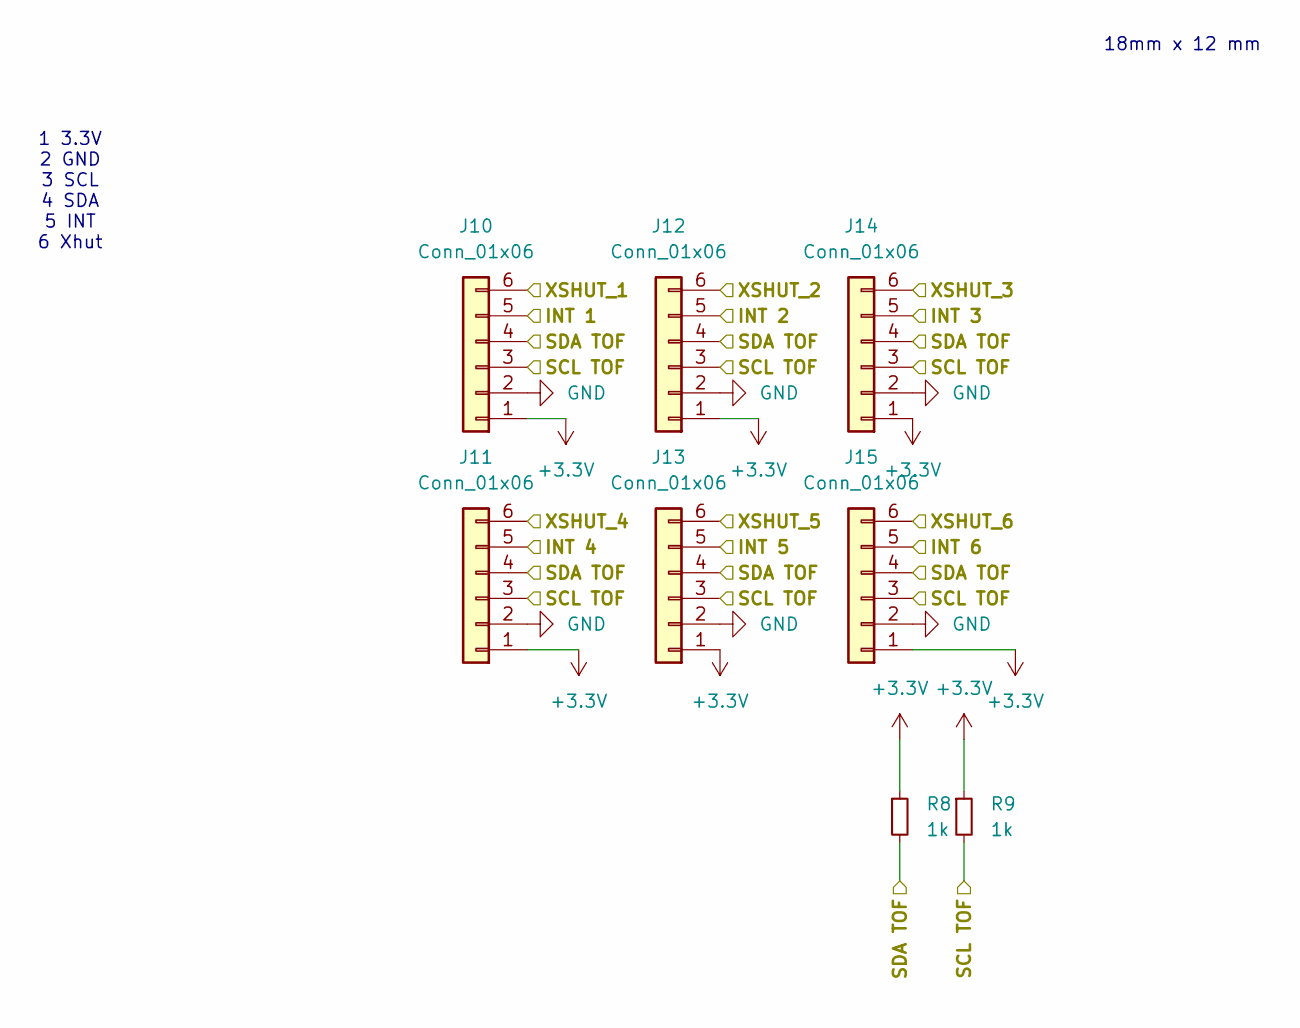
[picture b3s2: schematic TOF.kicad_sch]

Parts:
J10, J11, J12, J13, J14, J15: Conn_01x06; JST_SH_BM06B-SRSS-TB_1x06-1MP_P1.00mm_Vertical
R8, R9: 1k; R_0402_1005Metric

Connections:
+3.3V: J10.1, J11.1, J12.1, J13.1, J14.1, J15.1, R8.1, R9.1; also elsewhere on the board
GND: J10.2, J10.MP, J11.2, J11.MP, J12.2, J12.MP, J13.2, J13.MP, J14.2, J14.MP, J15.2, J15.MP; also elsewhere on the board
INT_1: J10.5; also elsewhere on the board
INT_2: J12.5; also elsewhere on the board
INT_3: J14.5; also elsewhere on the board
INT_4: J11.5; also elsewhere on the board
INT_5: J13.5; also elsewhere on the board
INT_6: J15.5; also elsewhere on the board
SCL TOF: J10.3, J11.3, J12.3, J13.3, J14.3, J15.3, R9.2; also elsewhere on the board
SDA TOF: J10.4, J11.4, J12.4, J13.4, J14.4, J15.4, R8.2; also elsewhere on the board
XSHUT_1: J10.6; also elsewhere on the board
XSHUT_2: J12.6; also elsewhere on the board
XSHUT_3: J14.6; also elsewhere on the board
XSHUT_4: J11.6; also elsewhere on the board
XSHUT_5: J13.6; also elsewhere on the board
XSHUT_6: J15.6; also elsewhere on the board

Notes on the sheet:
18mm x 12 mm
1 3.3V 2 GND 3 SCL 4 SDA 5 INT 6 Xhut

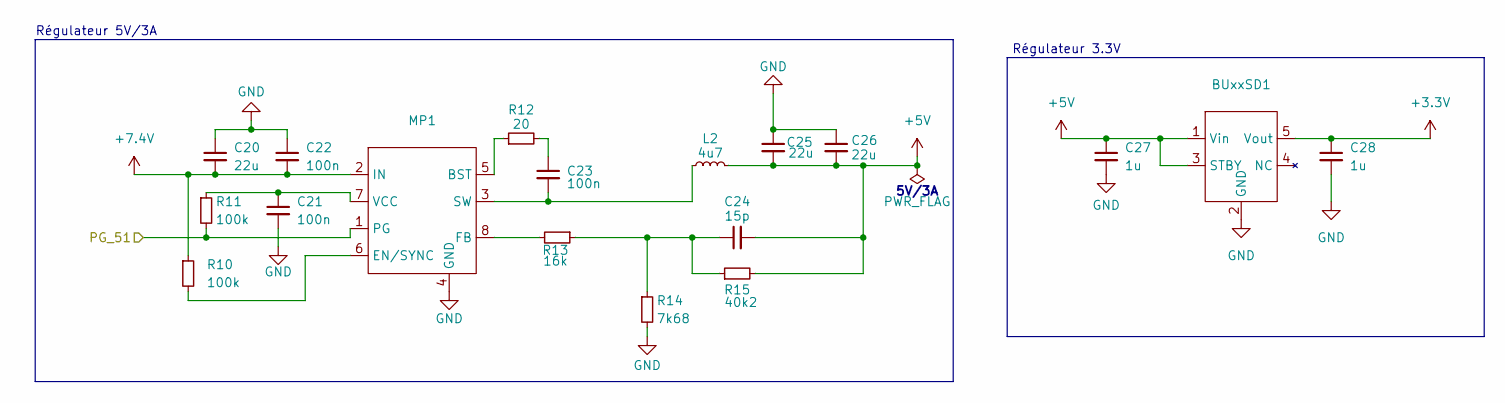
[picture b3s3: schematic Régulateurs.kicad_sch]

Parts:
BUxxSD1: SSOP5_BUxxSD5; MPN BU33SD5WG-TR
C20: 22u; C_1206_3216Metric
C21, C22, C23: 100n; C_0402_1005Metric
C24: 15p; C_0402_1005Metric
C25, C26: 22u; C_0603_1608Metric
C27, C28: 1u; C_0603_1608Metric
L2: 4u7; 74404054068
MP1: TSOT23-8; MPN MP1475DJ-LF-P
R10, R11: 100k; R_0402_1005Metric
R12: 20; R_0402_1005Metric
R13: 16k; R_0402_1005Metric
R14: 7k68; R_0402_1005Metric
R15: 40k2; R_0402_1005Metric

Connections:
+3.3V: BUxxSD1.5 (Vout), C28.1; also elsewhere on the board
+5V: BUxxSD1.1 (Vin), BUxxSD1.3 (STBY), C24.2, C25.2, C26.2, C27.1, L2.2, R15.2; also elsewhere on the board
+7.4V: C20.2, C22.2, MP1.2 (IN), R10.1; also elsewhere on the board
GND: BUxxSD1.2 (GND), C20.1, C21.2, C22.1, C25.1, C26.1, C27.2, C28.2, MP1.4 (GND), R14.2; also elsewhere on the board
unnamed: C23.1, R12.2
unnamed: C24.1, R13.1, R14.1, R15.1
unnamed: MP1.5 (BST), R12.1
unnamed: MP1.6 (EN/SYNC), R10.2
unnamed: MP1.8 (FB), R13.2
unnamed: C23.2, L2.1, MP1.3 (SW)
unnamed: C21.1, MP1.7 (VCC), R11.1
PG_51: MP1.1 (PG), R11.2; also elsewhere on the board

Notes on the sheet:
Régulateur 5V/3A
Régulateur 3.3V
5V/3A
